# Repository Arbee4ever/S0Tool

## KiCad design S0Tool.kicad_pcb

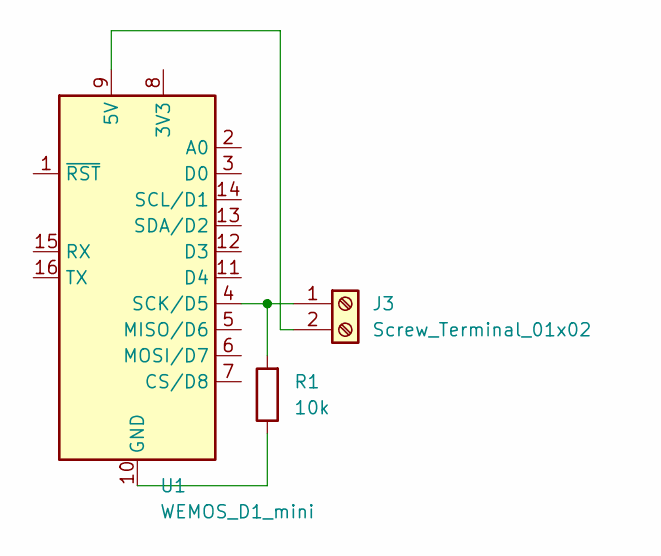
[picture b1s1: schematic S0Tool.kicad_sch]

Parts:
J3: Screw_Terminal_01x02; TerminalBlock_Phoenix_MKDS-1,5-2-5.08_1x02_P5.08mm_Horizont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
R1: 10k; R_Axial_DIN0411_L9.9mm_D3.6mm_P15.24mm_Horizontal
U1: WEMOS_D1_mini; WEMOS_D1_mini_light

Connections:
unnamed: J3.1, R1.2, U1.4 (SCK/D5)
unnamed: J3.2, U1.9 (5V)
unnamed: R1.1, U1.10 (GND)

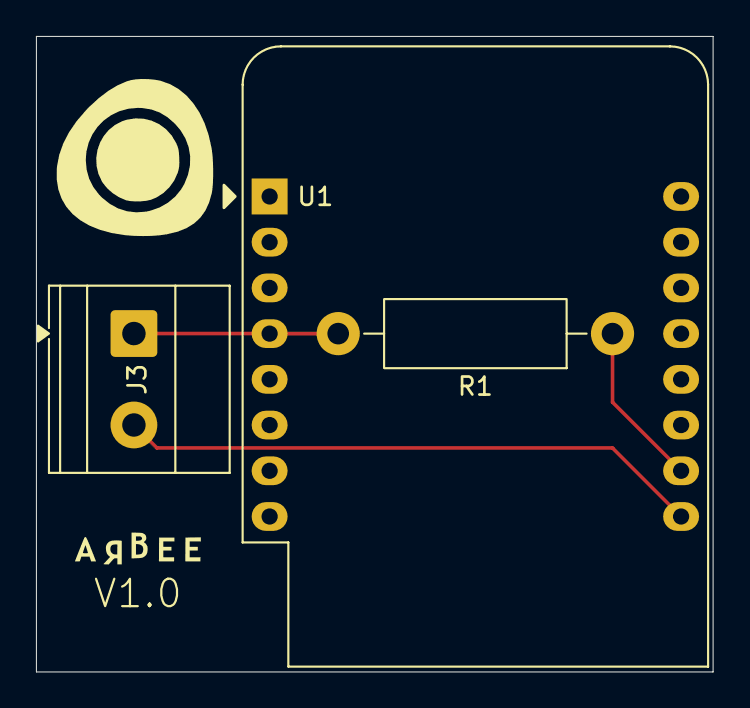
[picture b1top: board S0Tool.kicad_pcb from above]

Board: 2 copper layers, 37.6 x 35.3 mm, 3 parts (0 on the bottom side), 3 nets.
